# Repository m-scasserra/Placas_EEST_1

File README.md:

# Placas accesorios a Taller de la EEST N° 1

## Uso
En la carpeta de proyecto KiCad correspondiente se encuentra la carpeta "Placas PDF" donde ya esta exportado el archivo .pdf para imprimir y hacer la transferencia del cobre y de la serigrafia. La serigrafia ya se encuentra espejada.

## Lista de materiales
- 8 x Resistencias de 220 Ω 1/4 W
- 4 x Resistencias de 10 kΩ 1/4 W
- 8 x LEDs de 5mm
- 2 x Jumpers de 2.54mm
- 1 x tira de 40 pines rectos macho para PCB de 2.54mm
- 1 x tira de 40 pines rectos hembra para PCB de 2.54mm
- 4 x Pulsadores Tact Switch 6x6 de 4 pines
- 1 x Placa PCB de 10cm x 5cm
- 1 x Placa PCB de 5cm x 5cm

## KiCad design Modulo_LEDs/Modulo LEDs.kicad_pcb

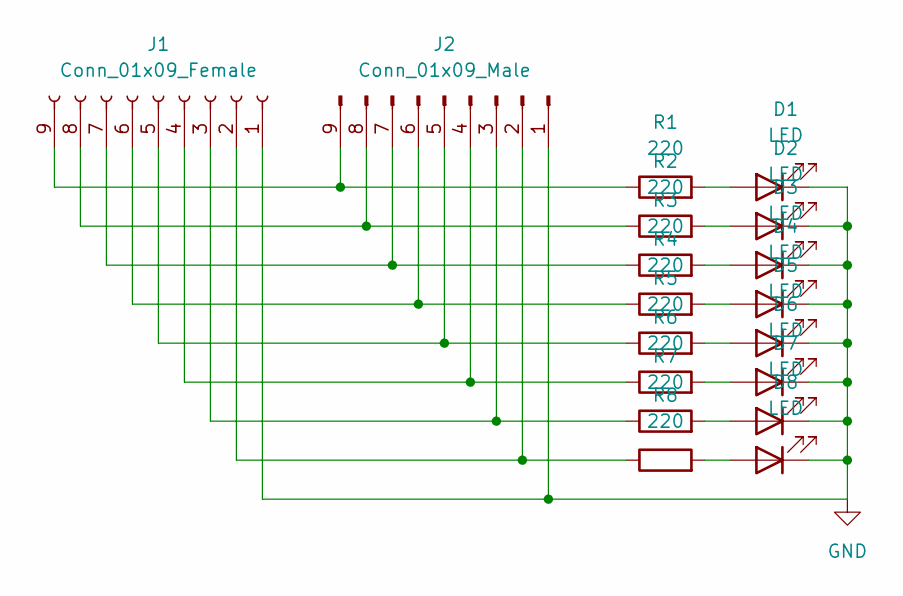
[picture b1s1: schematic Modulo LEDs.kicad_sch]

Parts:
D1, D2, D3, D4, D5, D6, D7, D8: LED; LED_D5.0mm
J1: Conn_01x09_Female; PinSocket_1x09_P2.54mm_Vertical
J2: Conn_01x09_Male; PinHeader_1x09_P2.54mm_Vertical
R1, R2, R3, R4, R5, R6, R7, R8: 220; R_Axial_DIN0207_L6.3mm_D2.5mm_P10.16mm_Horizontal

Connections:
GND: D1.1 (K), D2.1 (K), D3.1 (K), D4.1 (K), D5.1 (K), D6.1 (K), D7.1 (K), D8.1 (K), J1.1, J2.1
unnamed: D1.2 (A), R1.2
unnamed: D2.2 (A), R2.2
unnamed: D3.2 (A), R3.2
unnamed: D4.2 (A), R4.2
unnamed: D5.2 (A), R5.2
unnamed: D6.2 (A), R6.2
unnamed: D7.2 (A), R7.2
unnamed: D8.2 (A), R8.2
unnamed: J1.2, J2.2, R8.1
unnamed: J1.3, J2.3, R7.1
unnamed: J1.4, J2.4, R6.1
unnamed: J1.5, J2.5, R5.1
unnamed: J1.6, J2.6, R4.1
unnamed: J1.7, J2.7, R3.1
unnamed: J1.8, J2.8, R2.1
unnamed: J1.9, J2.9, R1.1

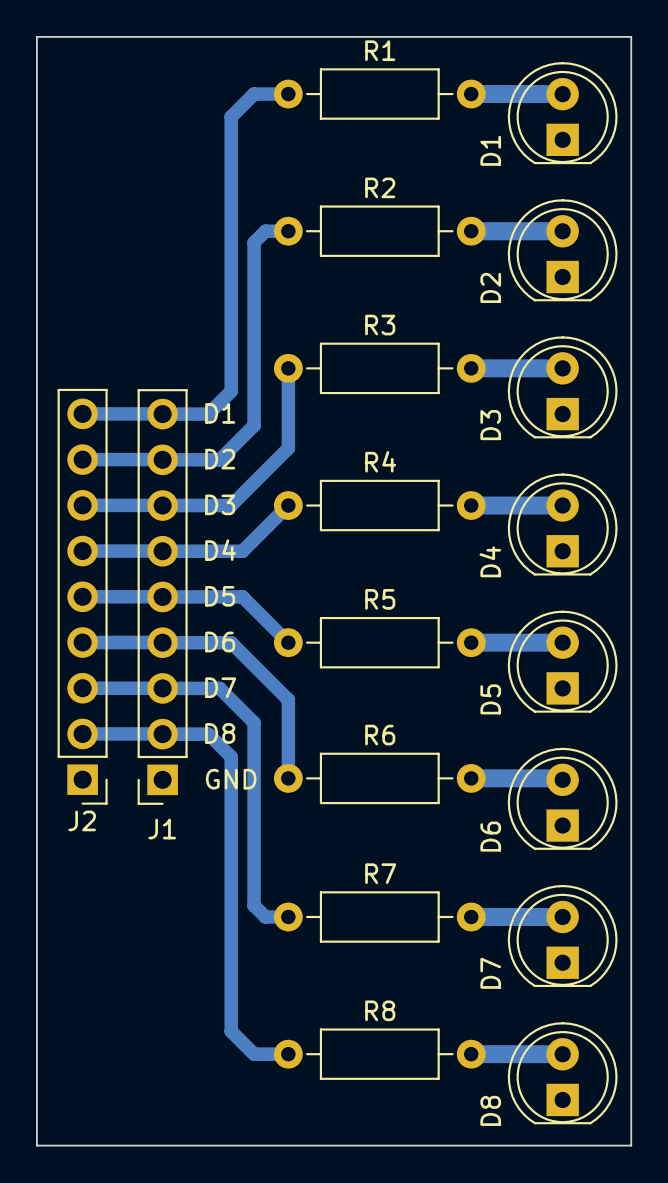
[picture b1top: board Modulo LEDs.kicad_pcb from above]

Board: 2 copper layers, 33.0 x 61.6 mm, 18 parts (0 on the bottom side), 17 nets.

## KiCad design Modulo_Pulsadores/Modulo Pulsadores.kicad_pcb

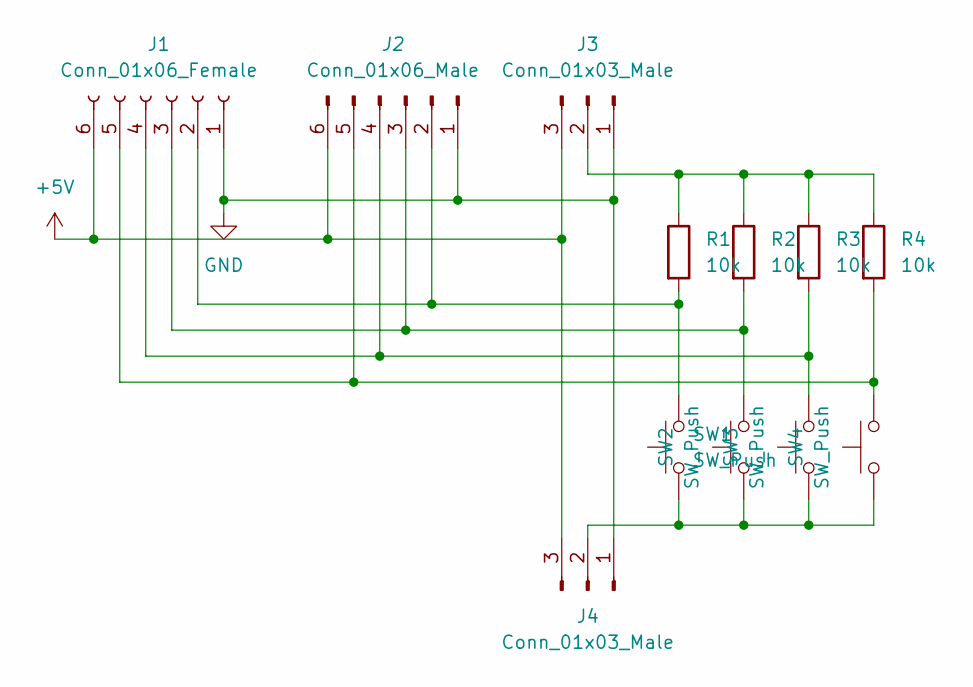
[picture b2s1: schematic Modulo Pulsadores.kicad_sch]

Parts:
J1: Conn_01x06_Female; PinSocket_1x06_P2.54mm_Vertical
J2: Conn_01x06_Male; PinHeader_1x06_P2.54mm_Vertical
J3, J4: Conn_01x03_Male; PinHeader_1x03_P2.54mm_Vertical
R1, R2, R3, R4: 10k; R_Axial_DIN0207_L6.3mm_D2.5mm_P10.16mm_Horizontal
SW1, SW2, SW3, SW4: SW_Push; SW_PUSH_6mm_H5mm

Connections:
+5V: J1.6, J2.6, J3.3, J4.3
GND: J1.1, J2.1, J3.1, J4.1
unnamed: J1.3, J2.3, R2.2, SW2.2
unnamed: J1.4, J2.4, R3.2, SW3.2
unnamed: J3.2, R1.1, R2.1, R3.1, R4.1
unnamed: J4.2, SW1.1, SW2.1, SW3.1, SW4.1
unnamed: J1.2, J2.2, R1.2, SW1.2
unnamed: J1.5, J2.5, R4.2, SW4.2

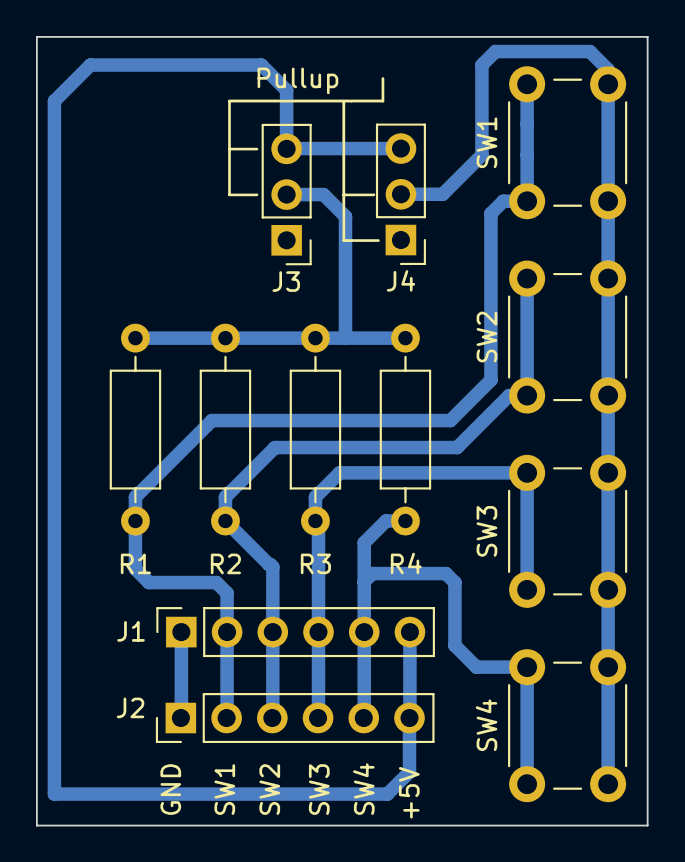
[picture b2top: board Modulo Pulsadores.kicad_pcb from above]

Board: 2 copper layers, 33.9 x 43.8 mm, 12 parts (0 on the bottom side), 8 nets.

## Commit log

2022-09-05 Rerouted Modulo Pulsadores
2022-09-06 Arreglado path de las carpetas, agregado el README.md y los archivos para la impresion
2022-09-06 Arreglado el README.md
2022-09-06 Agregado lista de materiales
2022-09-26 Fixed PCb
